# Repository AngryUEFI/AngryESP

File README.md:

# AngryESP

Control the power and reset PINs of an ATX mainboard via an ESP32.

## PCB
* prefer not to solder the ESP directly to the board, use sockets
* not all pins on the ESP socket need to be populated, only 2+4 are required
* if the pinout of your ESP does not match, connect the correct pins via jumper cables
* the buttons and the HDD LED are not required
* the power LED is required to drop the 5V of the LED pin to a safe value for the ESP (3.3V)
* connect the 5V and GND header to a USB header on the mainboard
* enable USB charging or Wake up by USB on the UEFI to power the USB ports when the system is off
* the 5V and GND pin rows are for connecting additional things, e.g. fans
* system header pins have an in and an out to allow connecting to the chassis as well
* reset and power button headers have one 3.3V pin, one GND pin, measure the pins to figure out which one is which if your mainboard does not document this

**Verify voltage levels of the buttons before connecting the ESP** The ESP only tolerates 3.3V. Your mainboard might use 5V on the buttons, this might damage the ESP.

Pin mappings for reference:

* GPIO18 - Reset
* GPIO21 - Short Power
* GPIO19 - Long Power
* GPIO5  - Power LED

Long power (6s press) and short power (0.2s press) use two different pins for easier setup in ESPHome. The two pins are shorted on the PCB and go to the power button header.

## ESPHome config
There are two options:
1. Home Assistant integrated
2. Standalone

### Home Assistant integrated
* adds the ESP to HA via the ESPHome integration
* buttons and LED are HA entities
* requires working HA
* control via API of HA

Use `ESPHome/ha.yaml` in the ESPHome Builder in HA. Create a new device and copy the contents of the `ha.yaml` into the file below the auto generated parts of the ESPHome config.

### Standalone
The `Standalone/` PlatformIO project ships a self-contained firmware that exposes a direct HTTP API for power control without Home Assistant. 
It supports ESP32 boards (untested) and the Arduino UNO R4 WiFi (tested, working).

* build with `pio run -e esp32doit-espduino` for ESP32 or `pio run -e uno_r4_wifi` for the UNO R4 WiFi
* upload with the matching `--target upload` command once the board is connected
* configure Wi-Fi credentials by creating `Standalone/include/wifi_config.h` before flashing (based on template in same folder)
* configure pins used on the board in `Standalone/include/pins_config.h` and the timing configuration for power cycling the experiment machine.
* HTTP API endpoints:
  * `POST /api/power/on` — tap the ATX power button (short pulse)
  * `POST /api/power/off` — hold the power header long enough for a hard shutdown (~6 s)
  * `POST /api/power/reset` — toggle the reset header
  * `GET /api/power/led` — read the live state of the power LED input
  * `POST /api/system/reboot` — reboot the controller itself
  * `GET /api/health` — Returns SSID details and IP

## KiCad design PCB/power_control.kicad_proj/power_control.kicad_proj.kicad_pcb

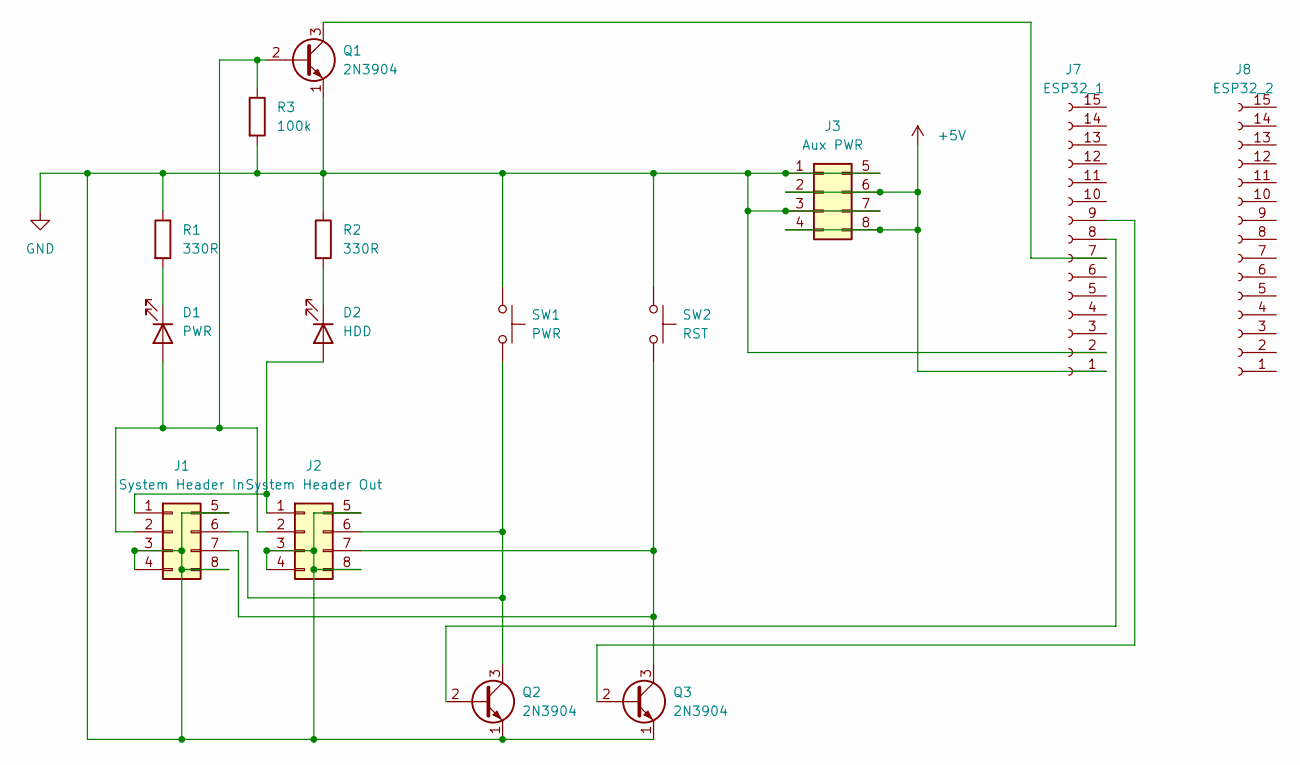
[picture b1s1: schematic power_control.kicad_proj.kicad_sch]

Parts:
D1: PWR; LED_D3.0mm
D2: HDD; LED_D3.0mm
J1: System Header In; PinHeader_2x04_P2.54mm_Vertical
J2: System Header Out; PinHeader_2x04_P2.54mm_Vertical
J3: Aux PWR; PinHeader_2x04_P2.54mm_Vertical
J7: ESP32_1; PinSocket_1x15_P2.54mm_Vertical
J8: ESP32_2; PinSocket_1x15_P2.54mm_Vertical
Q1, Q2, Q3: 2N3904; TO-92_Inline
R1, R2: 330R; R_Axial_DIN0207_L6.3mm_D2.5mm_P10.16mm_Horizontal
R3: 100k; R_Axial_DIN0207_L6.3mm_D2.5mm_P10.16mm_Horizontal
SW1: PWR; SW_PUSH_6mm
SW2: RST; SW_PUSH_6mm

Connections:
+5V: J3.2 (5V), J3.4 (5V), J3.6 (5V), J3.8 (5V), J7.1 (5V)
GND: J1.3 (GND), J1.4 (GND), J1.5 (GND), J1.8 (GND), J2.3 (GND), J2.4 (GND), J2.5 (GND), J2.8 (GND), J3.1 (GND), J3.3 (GND), J3.5 (GND), J3.7 (GND), J7.2 (GND), Q1.1 (E), Q2.1 (E), Q3.1 (E), R1.1, R2.1, R3.2, SW1.1, SW2.1
unnamed: D1.2 (A), J1.2 (PWR_LED+), J2.2 (PWR_LED+), Q1.2 (B), R3.1
unnamed: D1.1 (K), R1.2
unnamed: D2.2 (A), J1.1 (HDD+), J2.1 (HDD+)
unnamed: D2.1 (K), R2.2
unnamed: J1.6 (PWR_BTN+), J2.6 (PWR_BTN+), Q2.3 (C), SW1.2
unnamed: J1.7 (RST+), J2.7 (RST+), Q3.3 (C), SW2.2
unnamed: J7.8 (D25), Q2.2 (B)
unnamed: J7.7 (D26), Q1.3 (C)
unnamed: J7.9 (D33), Q3.2 (B)

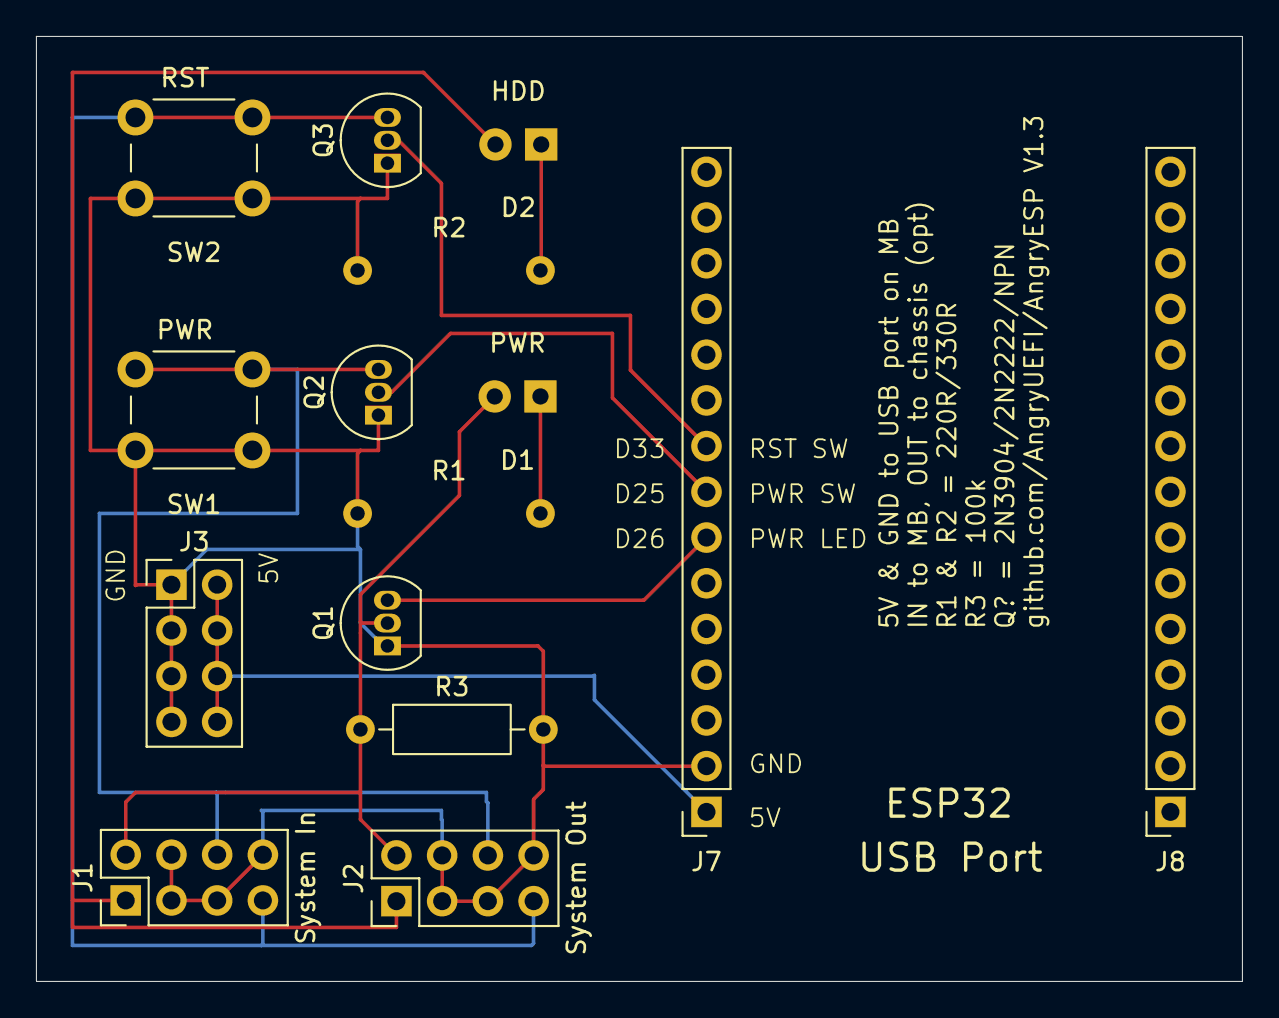
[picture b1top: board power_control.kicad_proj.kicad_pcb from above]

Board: 2 copper layers, 67.0 x 52.5 mm, 15 parts (0 on the bottom side), 11 nets.

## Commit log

2025-07-31 Verison 1.0 of PCB
2025-07-31 Add ESPHome HA config
2025-07-31 PCB v1.1, adjust pin markings
2025-07-31 Add images
2025-10-11 Added Standalone version for ESP32 and Arduino UNO R4 WiFi. See in top level, and in directory.
2025-12-16 Major rework of PCB, incompatible!
    use transistors to sense LED and switch pins
    add system header compatible with mainboard header
    move pins to one side -> only single header required
    we now need two PCB sides, yay
